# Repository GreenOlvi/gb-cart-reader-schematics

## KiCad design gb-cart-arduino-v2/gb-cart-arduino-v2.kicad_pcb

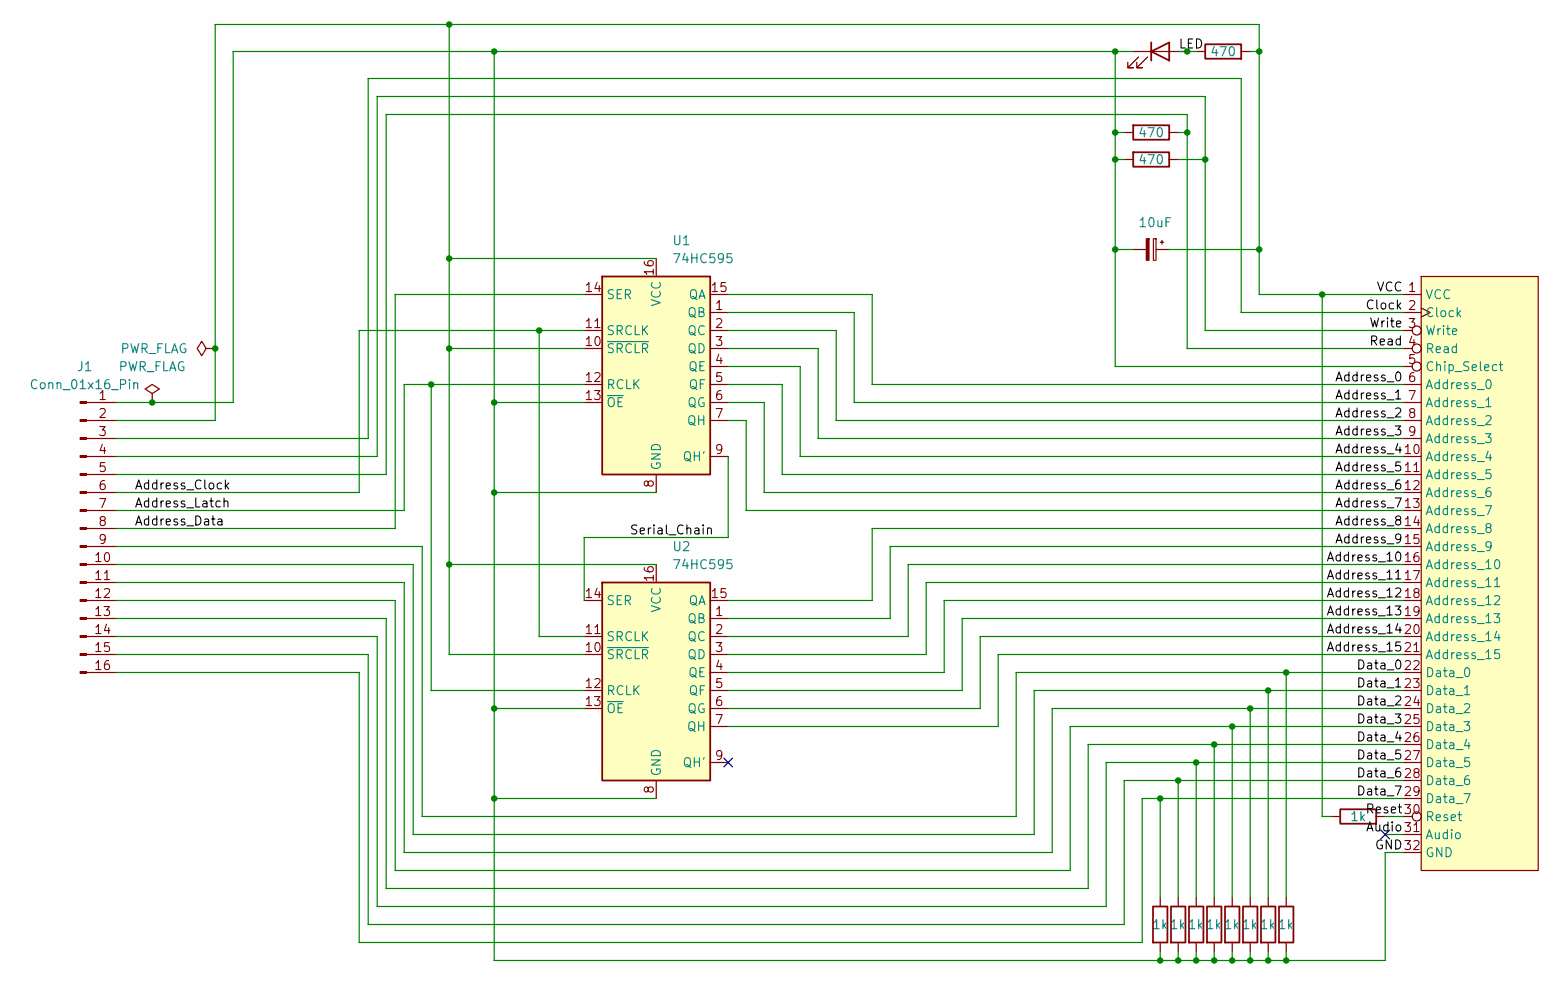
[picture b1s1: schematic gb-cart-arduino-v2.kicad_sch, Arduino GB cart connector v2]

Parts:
C1: 10uF; C_1206_3216Metric
D1: LED; LED_1206_3216Metric
J1: Conn_01x16_Pin; PinSocket_1x16_P2.54mm_Vertical
Rd0, Rd1, Rd2, Rd3, Rd4, Rd5, Rd6, Rd7: 1k; R_1206_3216Metric
Rl1: 470; R_1206_3216Metric
Rr1: 470; R_1206_3216Metric
Rreset1: 1k; R_1206_3216Metric
Rw1: 470; R_1206_3216Metric
U1, U2: 74HC595; SOP-16_4.4x10.4mm_P1.27mm
U3: Gameboy cartridge connector

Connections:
/Address_0: U1.15 (QA), U3.6 (Address_0)
/Address_1: U1.1 (QB), U3.7 (Address_1)
/Address_2: U1.2 (QC), U3.8 (Address_2)
/Address_3: U1.3 (QD), U3.9 (Address_3)
/Address_4: U1.4 (QE), U3.10 (Address_4)
/Address_5: U1.5 (QF), U3.11 (Address_5)
/Address_6: U1.6 (QG), U3.12 (Address_6)
/Address_7: U1.7 (QH), U3.13 (Address_7)
/Address_8: U2.15 (QA), U3.14 (Address_8)
/Address_9: U2.1 (QB), U3.15 (Address_9)
/Address_10: U2.2 (QC), U3.16 (Address_10)
/Address_11: U2.3 (QD), U3.17 (Address_11)
/Address_12: U2.4 (QE), U3.18 (Address_12)
/Address_13: U2.5 (QF), U3.19 (Address_13)
/Address_14: U2.6 (QG), U3.20 (Address_14)
/Address_15: U2.7 (QH), U3.21 (Address_15)
/Address_Clock: J1.6, U1.11 (SRCLK), U2.11 (SRCLK)
/Address_Data: J1.8, U1.14 (SER)
/Address_Latch: J1.7, U1.12 (RCLK), U2.12 (RCLK)
/Audio: U3.31 (Audio)
/Clock: J1.3, U3.2 (Clock)
/Data_0: J1.9, Rd0.1, U3.22 (Data_0)
/Data_1: J1.10, Rd1.1, U3.23 (Data_1)
/Data_2: J1.11, Rd2.1, U3.24 (Data_2)
/Data_3: J1.12, Rd3.1, U3.25 (Data_3)
/Data_4: J1.13, Rd4.1, U3.26 (Data_4)
/Data_5: J1.14, Rd5.1, U3.27 (Data_5)
/Data_6: J1.15, Rd6.1, U3.28 (Data_6)
/Data_7: J1.16, Rd7.1, U3.29 (Data_7)
/GND: C1.2, D1.1 (K), J1.1, Rd0.2, Rd1.2, Rd2.2, Rd3.2, Rd4.2, Rd5.2, Rd6.2, Rd7.2, Rr1.2, Rw1.2, U1.8 (GND), U1.13 (~OE), U2.8 (GND), U2.13 (~OE), U3.5 (Chip_Select), U3.32 (GND)
/LED: D1.2 (A), Rl1.1
/Read: J1.5, Rr1.1, U3.4 (Read)
/Reset: Rreset1.2, U3.30 (Reset)
/Serial_Chain: U1.9 (QH'), U2.14 (SER)
/VCC: C1.1, J1.2, Rl1.2, Rreset1.1, U1.10 (~SRCLR), U1.16 (VCC), U2.10 (~SRCLR), U2.16 (VCC), U3.1 (VCC)
/Write: J1.4, Rw1.1, U3.3 (Write)

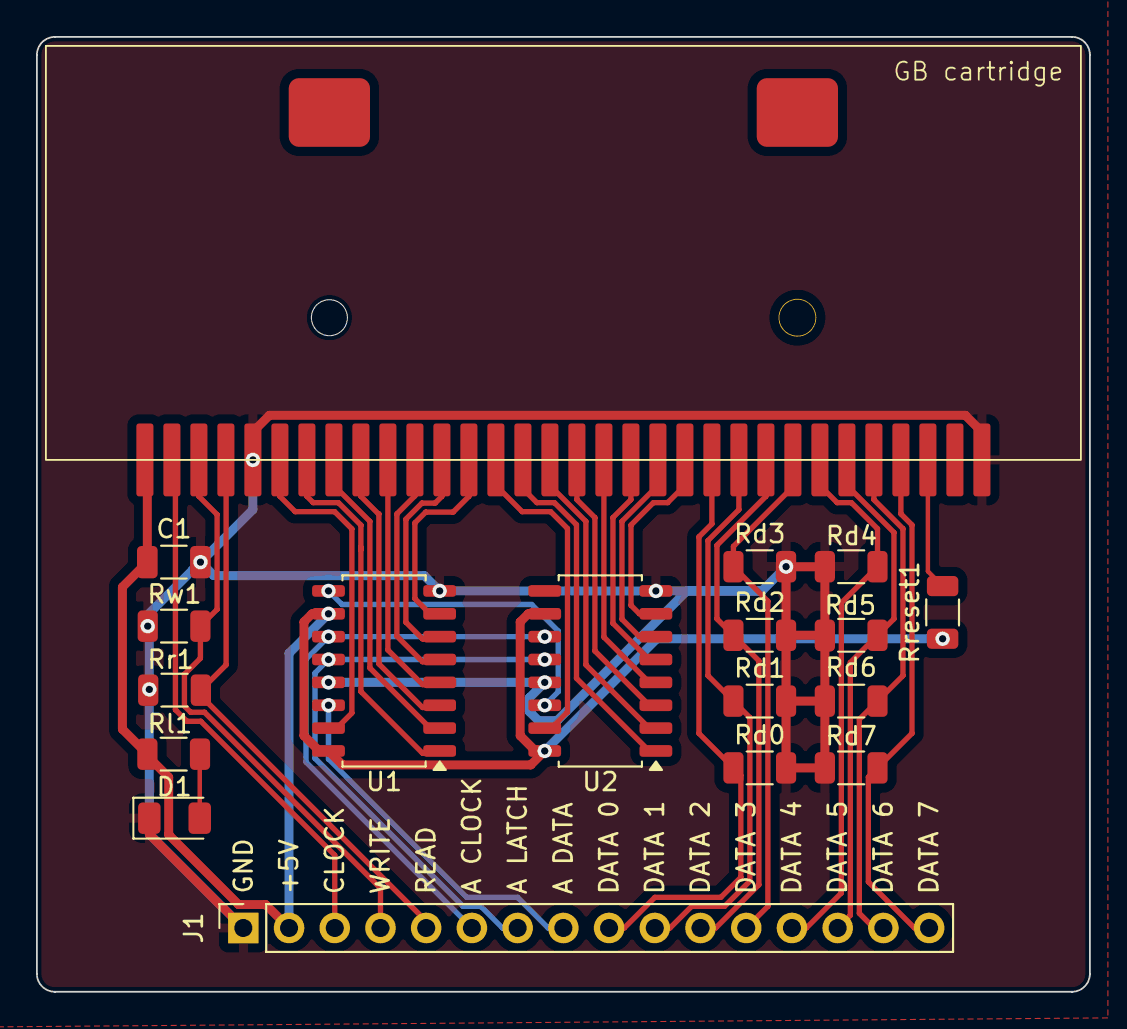
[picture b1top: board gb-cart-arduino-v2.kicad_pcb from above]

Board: 2 copper layers, 58.5 x 53.0 mm, 18 parts (0 on the bottom side), 35 nets.

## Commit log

2025-11-11 Added reader v2
2025-11-11 Rewired v2
2025-11-11 Added texts
2025-11-13 Final sent to production
2025-11-27 Reversed gb cart connector footprint
2025-11-29 Moved connector definition to project
2025-11-30 Final v2.1
2025-12-07 Added workflow for gerber files
2025-12-07 Added manual run for workflow
2025-12-07 Run on kicad image
